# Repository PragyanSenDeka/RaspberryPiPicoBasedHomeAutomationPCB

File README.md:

PicoW Smart Home Automation Controller

A robust home automation controller built around the Raspberry Pi Pico W, designed for reliable operation in real-world environments. It combines industrial communication (MODBUS over RS485) with modern IoT capabilities, making it suitable for smart homes, labs, and distributed control systems.

Features

Raspberry Pi Pico W (or compatible variants) for wireless connectivity

RS485 / MODBUS interface for industrial-grade communication

DIP switch-based MODBUS address selection for easy multi-node deployment

SHT31-DIS high-precision temperature and humidity sensor

QWIIC connector for plug-and-play I2C expansion

Reset button and user button for control and interaction

User RGB LED for status indication and debugging

2x5 SPI expansion header for additional peripherals

High-power relay (230V, 16A) for controlling appliances

Wide input voltage support: 8V to 24V DC

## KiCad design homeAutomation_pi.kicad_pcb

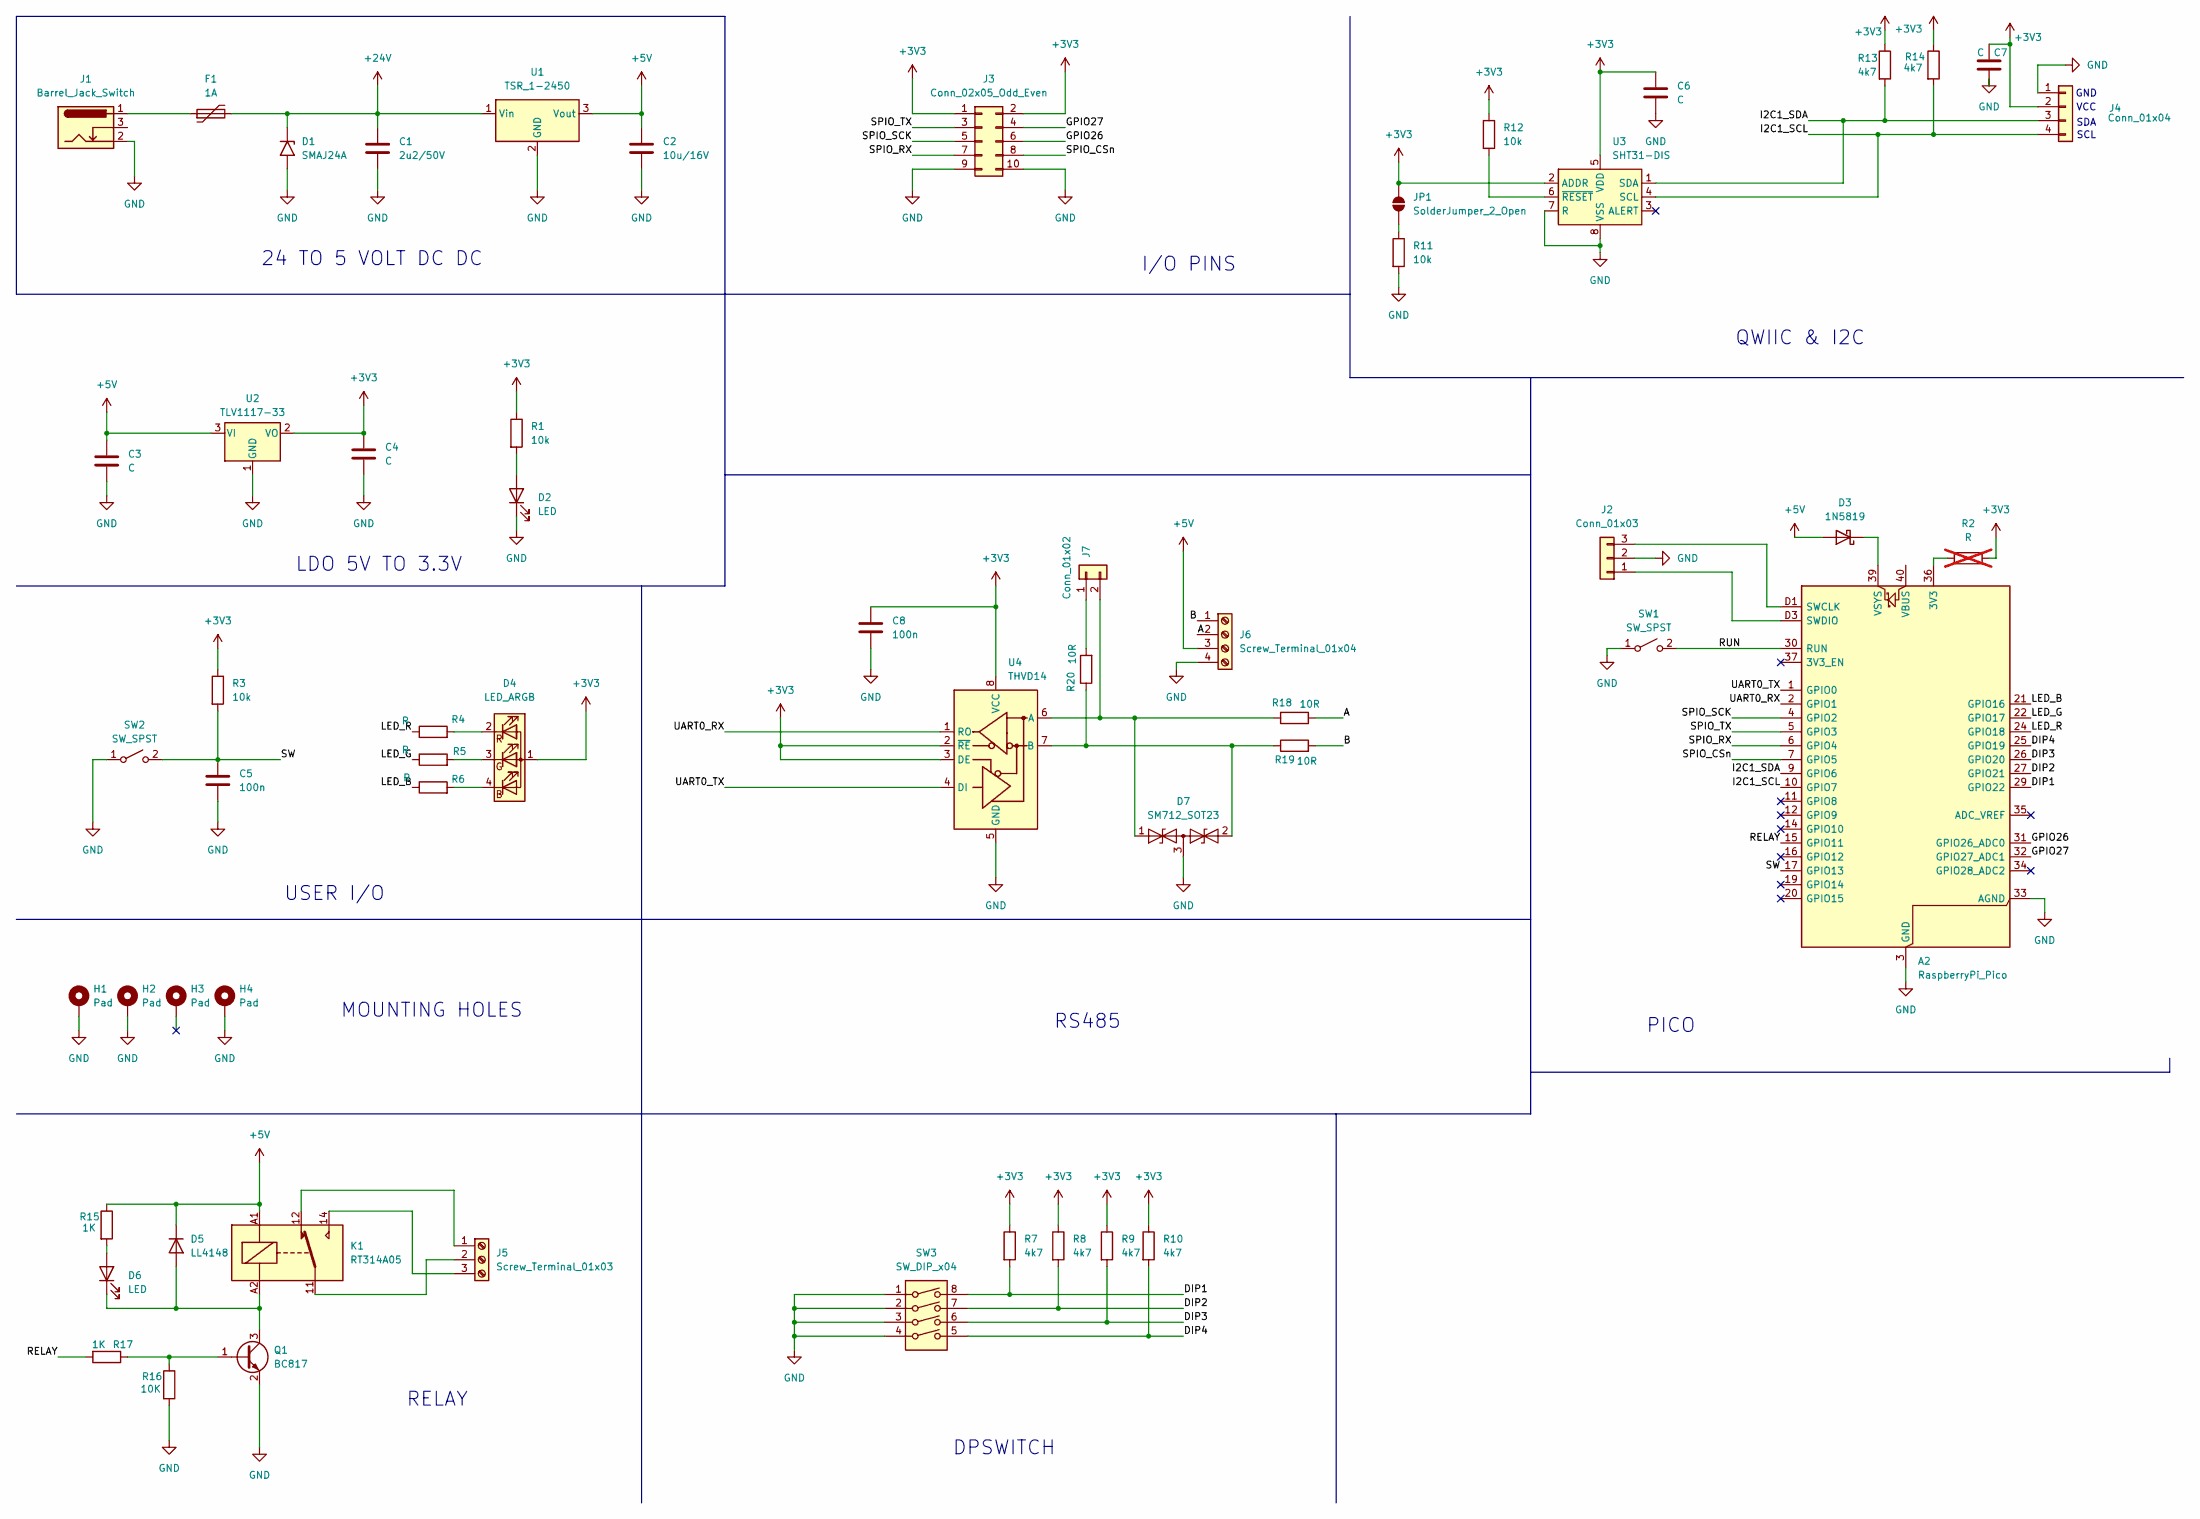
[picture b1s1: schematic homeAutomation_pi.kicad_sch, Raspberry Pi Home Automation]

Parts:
A2: RaspberryPi_Pico; RaspberryPi_Pico_SMD_HandSolder
C1: 2u2/50V; C_0805_2012Metric_Pad1.18x1.45mm_HandSolder
C2: 10u/16V; C_0805_2012Metric_Pad1.18x1.45mm_HandSolder
C3, C4, C6, C7: C; C_0805_2012Metric_Pad1.18x1.45mm_HandSolder
C5, C8: 100n; C_0805_2012Metric_Pad1.18x1.45mm_HandSolder
D1: SMAJ24A; D_SMA
D2: LED; LED_0201_0603Metric_Pad0.64x0.40mm_HandSolder
D3: 1N5819; D_DO-41_SOD81_P10.16mm_Horizontal
D4: LED_ARGB; LED_Cree-PLCC4_3.2x2.8mm_CCW
D5: LL4148; D_MiniMELF
D6: LED; LED_0805_2012Metric_Pad1.15x1.40mm_HandSolder
D7: SM712_SOT23; SOT-23
F1: 1A; Fuse_0805_2012Metric_Pad1.15x1.40mm_HandSolder
H1, H2, H3, H4: Pad; MountingHole_3.2mm_M3_Pad
J1: Barrel_Jack_Switch; BarrelJack_Wuerth_6941xx301002
J2: Conn_01x03; PinHeader_1x03_P2.54mm_Vertical
J3: Conn_02x05_Odd_Even; PinHeader_2x05_P2.54mm_Vertical
J4: Conn_01x04; PinHeader_1x04_P2.54mm_Vertical
J5: Screw_Terminal_01x03; TerminalBlock_Phoenix_PT-1,5-3-5.0-H_1x03_P5.00mm_Horizontal
J6: Screw_Terminal_01x04; TerminalBlock_Phoenix_MKDS-1-4-3.81_1x04_P3.81mm_Horizontal
J7: Conn_01x02; PinHeader_1x02_P2.54mm_Vertical
JP1: SolderJumper_2_Open; SolderJumper-2_P1.3mm_Open_RoundedPad1.0x1.5mm
K1: RT314A05; Relay_SPDT_Schrack-RT1-16A-FormC_RM5mm
Q1: BC817; SOT-23
R1, R3, R11, R12: 10k; R_1206_3216Metric_Pad1.30x1.75mm_HandSolder
R2: R; R_1206_3216Metric_Pad1.30x1.75mm_HandSolder; not fitted
R4, R5, R6: R; R_1206_3216Metric_Pad1.30x1.75mm_HandSolder
R7, R8, R9, R10, R13, R14: 4k7; R_1206_3216Metric_Pad1.30x1.75mm_HandSolder
R15, R17: 1K; R_1206_3216Metric_Pad1.30x1.75mm_HandSolder
R16: 10K; R_1206_3216Metric_Pad1.30x1.75mm_HandSolder
R18, R19, R20: 10R; R_1206_3216Metric_Pad1.30x1.75mm_HandSolder
SW1, SW2: SW_SPST; SW_TH_Tactile_Omron_B3F-100x
SW3: SW_DIP_x04; SW_DIP_SPSTx04_Slide_Omron_A6S-410x_W8.9mm_P2.54mm
U1: TSR_1-2450; Converter_DCDC_TRACO_TSR-1_THT
U2: TLV1117-33; SOT-223-3_TabPin2
U3: SHT31-DIS; Sensirion_DFN-8-1EP_2.5x2.5mm_P0.5mm_EP1.1x1.7mm
U4: THVD14; SOIC-8_3.9x4.9mm_P1.27mm

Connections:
+3V3: C4.1, C6.1, C7.1, C8.1, D4.1 (A), J3.1, J3.2, J4.2, JP1.2 (B), R1.1, R2.2, R3.1, R7.1, R8.1, R9.1, R10.1, R12.1, R13.1, R14.1, U2.2 (VO), U3.2 (ADDR), U3.5 (VDD), U4.2 (~RE), U4.3 (DE), U4.8 (VCC)
+5V: C2.1, C3.1, D3.2 (A), D5.1 (K), J6.3, K1.A1, R15.1, U1.3 (Vout), U2.3 (VI)
+24V: C1.1, D1.1 (A1), F1.2, U1.1 (Vin)
/A: J6.2, R18.2
/B: J6.1, R19.2
/DIP1: A2.29 (GPIO22), R7.2, SW3.8
/DIP2: A2.27 (GPIO21), R8.2, SW3.7
/DIP3: A2.26 (GPIO20), R9.2, SW3.6
/DIP4: A2.25 (GPIO19), R10.2, SW3.5
/GPIO26: A2.31 (GPIO26_ADC0), J3.6
/GPIO27: A2.32 (GPIO27_ADC1), J3.4
/I2C1_SCL: A2.10 (GPIO7), J4.4, R14.2, U3.4 (SCL)
/I2C1_SDA: A2.9 (GPIO6), J4.3, R13.2, U3.1 (SDA)
/LED_B: A2.21 (GPIO16), R6.1
/LED_G: A2.22 (GPIO17), R5.1
/LED_R: A2.24 (GPIO18), R4.1
/RELAY: A2.15 (GPIO11), R17.2
/RUN: A2.30 (RUN), SW1.2 (B)
/SPIO_CSn: A2.7 (GPIO5), J3.8
/SPIO_RX: A2.6 (GPIO4), J3.7
/SPIO_SCK: A2.4 (GPIO2), J3.5
/SPIO_TX: A2.5 (GPIO3), J3.3
/SW: A2.17 (GPIO13), C5.1, R3.2, SW2.2 (B)
/UART0_RX: A2.2 (GPIO1), U4.1 (RO)
/UART0_TX: A2.1 (GPIO0), U4.4 (DI)
GND: A2.3 (GND), A2.8 (GND), A2.13 (GND), A2.18 (GND), A2.23 (GND), A2.28 (GND), A2.33 (AGND), A2.38 (GND), A2.D2 (GND), C1.2, C2.2, C3.2, C4.2, C5.2, C6.2, C7.2, C8.2, D1.2 (A2), D2.1 (K), D7.3 (common), H1.1, H2.1, H3.1, H4.1, J1.2, J2.2, J3.9, J3.10, J4.1, J6.4, Q1.2 (E), R11.2, R16.2, SW1.1 (A), SW2.1 (A), SW3.1, SW3.2, SW3.3, SW3.4, U1.2 (GND), U2.1 (GND), U3.7 (R), U3.8 (VSS), U3.9 (VSS), U4.5 (GND)
unnamed: A2.36 (3V3), R2.1
unnamed: A2.D1 (SWCLK), J2.3
unnamed: A2.D3 (SWDIO), J2.1
unnamed: A2.39 (VSYS), D3.1 (K)
unnamed: D2.2 (A), R1.2
unnamed: D4.4 (BK), R6.2
unnamed: D4.3 (GK), R5.2
unnamed: D4.2 (RK), R4.2
unnamed: D5.2 (A), D6.1 (K), K1.A2, Q1.3 (C)
unnamed: D6.2 (A), R15.2
unnamed: D7.1 (A1), J7.2, R18.1, U4.6 (A)
unnamed: D7.2 (A2), R19.1, R20.1, U4.7 (B)
unnamed: F1.1, J1.1
unnamed: J5.1, K1.12
unnamed: J5.2, K1.11
unnamed: J5.3, K1.14
unnamed: J7.1, R20.2
unnamed: JP1.1 (A), R11.1
unnamed: Q1.1 (B), R16.1, R17.1
unnamed: R12.2, U3.6 (~RESET)

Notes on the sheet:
VCC
MOUNTING HOLES
SCL
SDA
USER I/O
PICO
RS485
LDO 5V TO 3.3V
GND
QWIIC & I2C
RELAY
DPSWITCH
I/O PINS
24 TO 5 VOLT DC DC

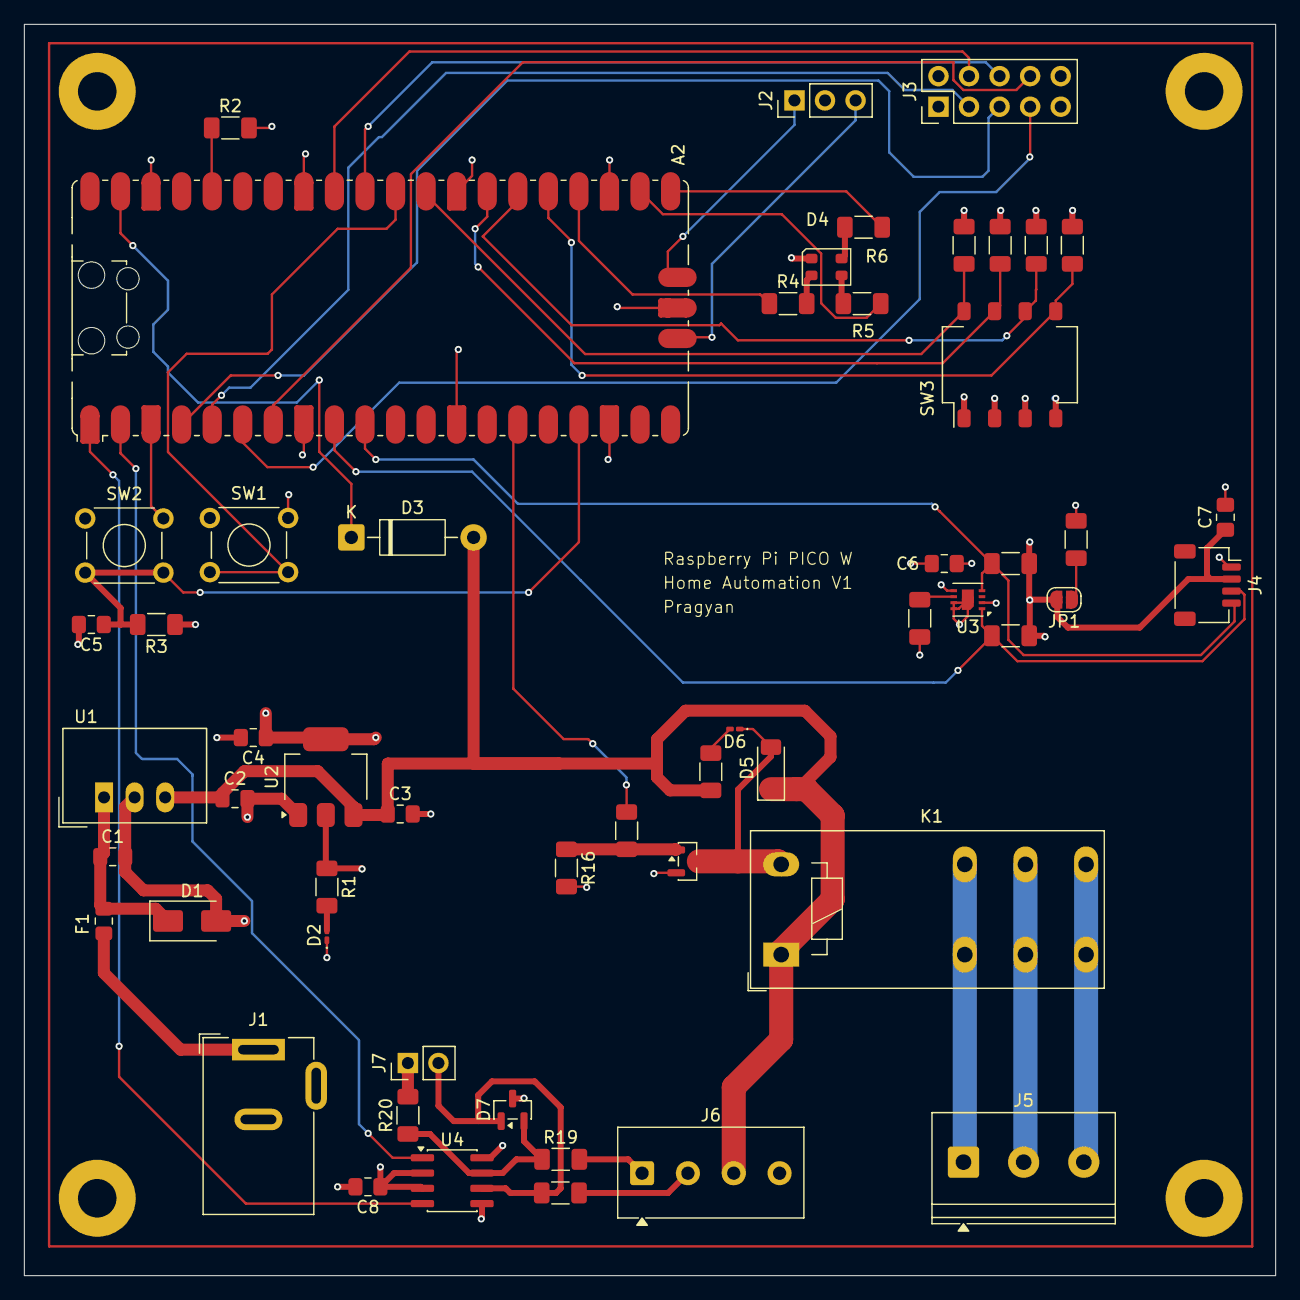
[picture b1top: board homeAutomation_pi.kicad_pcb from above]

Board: 4 copper layers, 104.0 x 104.0 mm, 58 parts (0 on the bottom side), 46 nets.

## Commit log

2026-03-18 added photos
2026-03-18 updated photos
